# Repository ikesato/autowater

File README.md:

概要
====

PIC を使った自動水やりきです。
毎日定時になると自動で水をプランターにまきます。

- マイコン : PIC12F1822
- ディスプレイ : AQM0802A-RN-GBW  
  I2C接続小型キャラクタLCDモジュール 8x2行 (秋月電気で購入)
- リアルタイムクロック :RTC-8564NB  
  リアルタイムクロック(RTC)モジュール
- ポンプ部 : 1000円ぐらいの灯油ポンプ

機能
====

- 時計機能
- アラーム機能  
 毎日指定した時間になると灯油ポンプから水を汲み上げます。
- 電源ONの時間設定  
 アラームがONの場合、電源ONしている時間を 0〜99秒で指定可能。

回路図
======

**全体**  

**LCD部**  

Board
=====

**全体**  

**LCD部**  

写真
====

**実装写真**  

参考
====

このシステムを作成するにあたり参考にしたサイトです。  
先人たちの力がないと実現できませんでした。ありがとうございました。

- きむ茶工房ガレージハウス  
 http://www.geocities.jp/zattouka/GarageHouse/index.htm  
 i2c 通信について参考にさせていただきました
- DIYカーメンテナンス 破壊班のブログ  
 http://diy-carmaintenance.com/ep-304bc/  
 灯油ポンプの分解方法など

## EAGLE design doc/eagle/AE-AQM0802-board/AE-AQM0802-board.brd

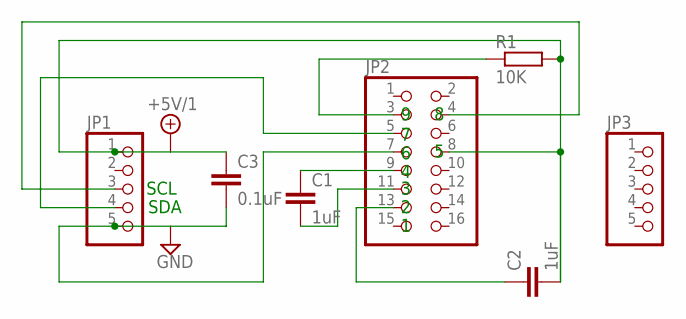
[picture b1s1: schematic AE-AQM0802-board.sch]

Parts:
C1, C2: 1uF; C0504
C3: 0.1uF; C0504
JP1, JP3: PINHD-1X5; 1X05
JP2: PINHD-2X8; 2X08
R1: 10K; M2012

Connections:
+5V/1: C2.2, C3.1, JP1.1, JP2.8, R1.2
GND: C3.2, JP1.5, JP2.7
unnamed: C1.2, JP2.11
unnamed: C2.1, JP2.13
unnamed: C1.1, JP2.9
unnamed: JP2.3, R1.1
unnamed: JP1.3, JP2.4
unnamed: JP1.4, JP2.5

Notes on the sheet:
SCL
SDA

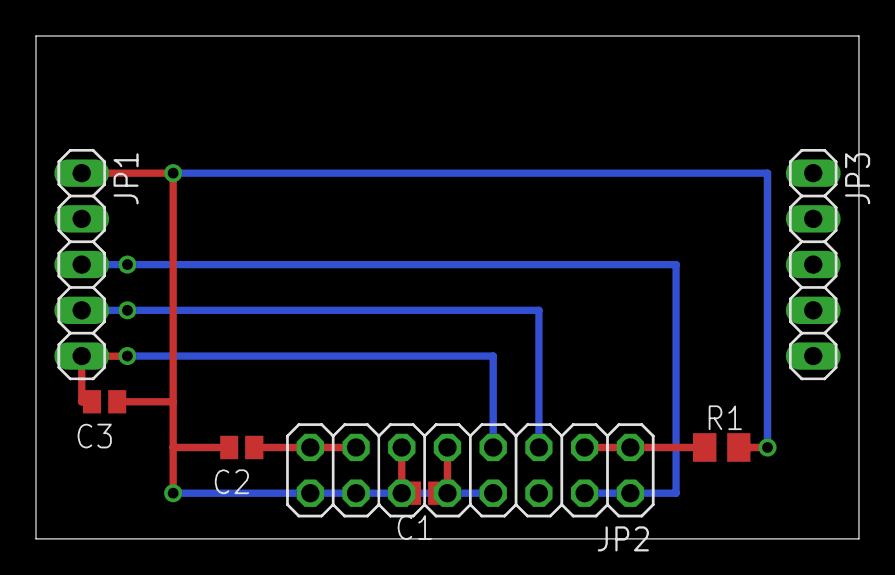
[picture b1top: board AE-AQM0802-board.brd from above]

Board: 2 copper layers, 45.7 x 27.9 mm, 7 parts (0 on the bottom side), 8 nets.

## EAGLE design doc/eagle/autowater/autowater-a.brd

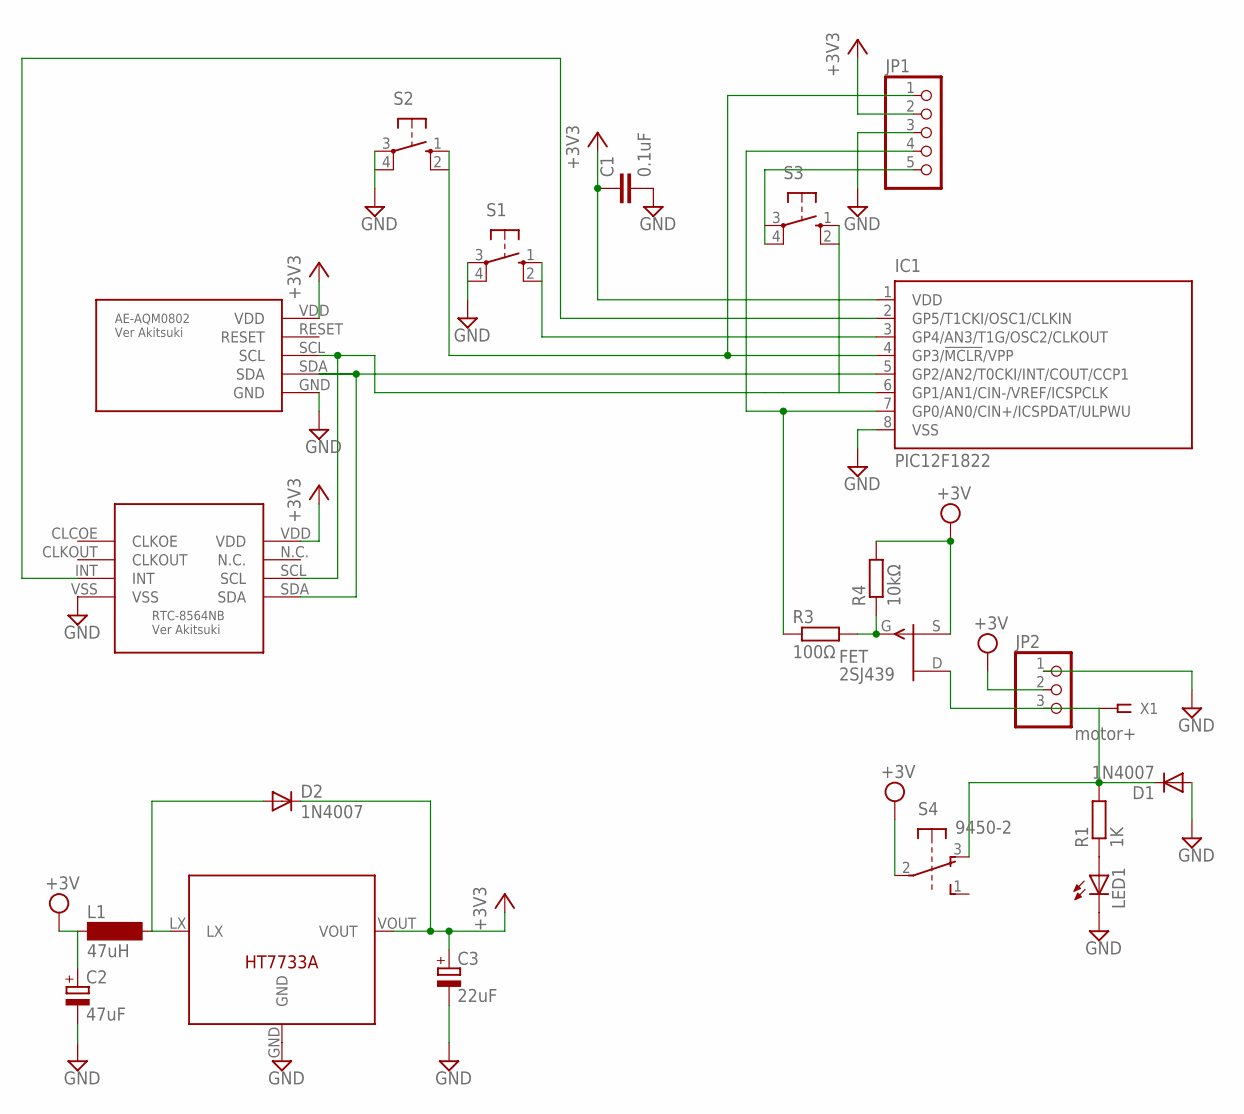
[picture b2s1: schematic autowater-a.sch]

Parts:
C1: 0.1uF; C7.5B3
C2: 47uF; TT2D5
C3: 22uF; TT2D5
D1, D2: 1N4007; DO35-7
FET: 2SJ439
IC1: PIC12F1822; DIL8; MPN PIC12F1822
JP1: PINHD-1X5; 1X05
JP2: PINHD-1X3; 1X03
L1: 47uH; SD75
LED1: LEDLZR181; LZR181
R1: 1K; 0204/7
R3: 100Ω; 0207/12
R4: 10kΩ; 0204/7
S1, S3: 10-XX; B3F-10XX; MPN B3F-1000
S2: 10-XX; B3F-10XX
S4: 9450-2
U$1: RTC-8564NB-VER-AKITSUKI
U$2: AE-AQM0802-VER-AKITSUKI
U$4: HT7733A
X1: motor+; SSW-101-02-S-S

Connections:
+3V3: C1.1, C3.+, D2.C, IC1.1 (VDD), JP1.2, U$1.VDD, U$2.VDD, U$4.VOUT
GND: C1.2, C2.-, C3.-, D1.A, IC1.8 (VSS), JP1.3, JP2.1, LED1.K (C), S1.3, S2.3, U$1.VSS, U$2.GND, U$4.GND
unnamed: IC1.5 (GP2/AN2/T0CKI/INT/COUT/CCP1), U$1.SDA, U$2.SDA
unnamed: IC1.2 (GP5/T1CKI/OSC1/CLKIN), U$1.INT
unnamed: JP1.5, S3.4 (P1)
unnamed: IC1.6 (GP1/AN1/CIN-/VREF/ICSPCLK), S3.1 (S), U$1.SCL, U$2.SCL
unnamed: IC1.3 (GP4/AN3/T1G/OSC2/CLKOUT), S1.1 (S)
unnamed: IC1.4 (GP3/!MCLR!/VPP), JP1.1, S2.1 (S)
unnamed: LED1.A, R1.1
unnamed: D1.C, FET.D, JP2.3, R1.2, S4.3 (O), X1.1
unnamed: IC1.7 (GP0/AN0/CIN+/ICSPDAT/ULPWU), JP1.4, R3.1
unnamed: D2.A, L1.2, U$4.LX
unnamed: FET.G, R3.2, R4.1
VCC: C2.+, FET.S, JP2.2, L1.1, R4.2, S4.2

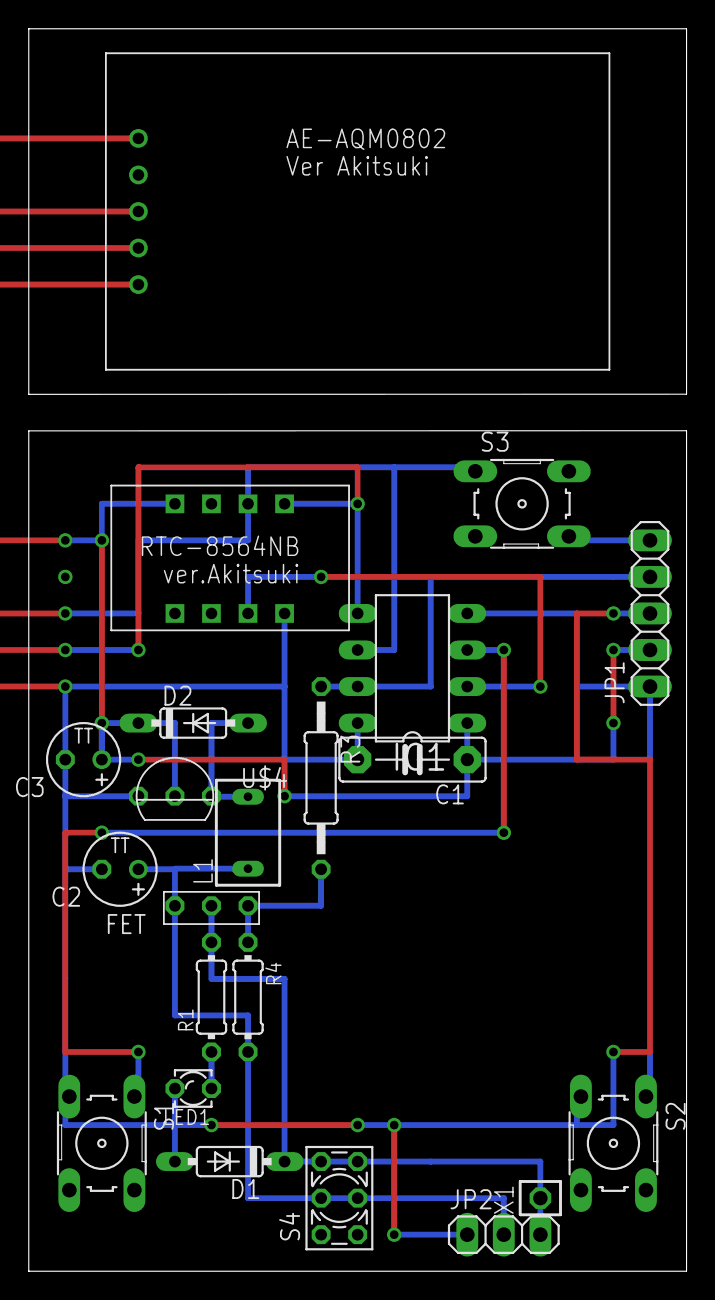
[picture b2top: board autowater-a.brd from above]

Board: 2 copper layers, 45.7 x 86.4 mm, 22 parts (0 on the bottom side), 14 nets.

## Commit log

2014-10-14 Add documents
